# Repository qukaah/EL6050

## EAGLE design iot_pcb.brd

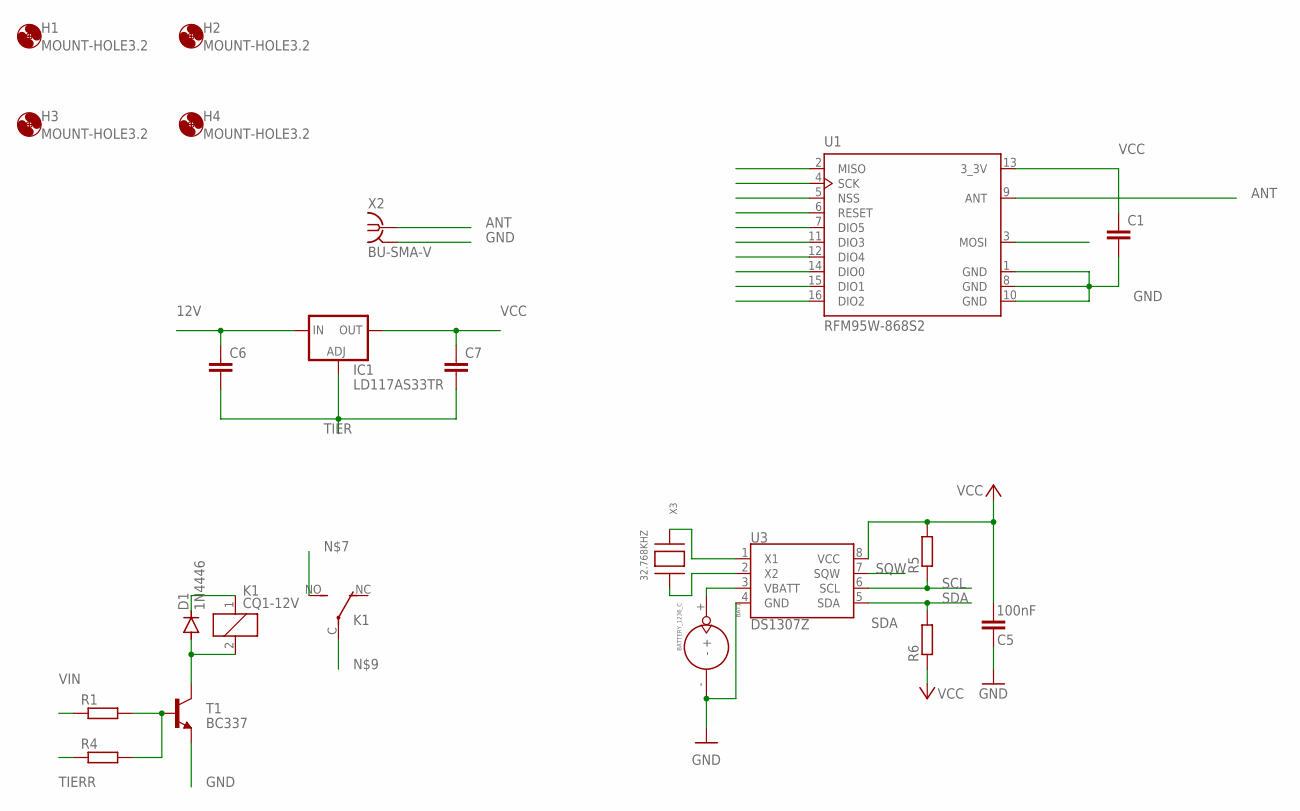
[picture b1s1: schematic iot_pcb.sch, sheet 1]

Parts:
BAT1: BATTERY_1236_C
C1, C6, C7: C-EU050-025X075; C050-025X075
C5: 100nF; C0603
D1: 1N4446; DO35-10
H1, H2, H3, H4: MOUNT-HOLE3.2; 3,2
IC1: LD117AS33TR; SOT223
K1: CQ1-12V; CQ1
R1, R4, R5, R6: R-EU_0207/10; 0207/10
T1: BC337; TO92
U1: RFM95W-868S2; XCVR_RFM95W-868S2
U3: DS1307Z; SO08-0.15
X2: BU-SMA-V
X3: 32.768KHZ; XTAL3215

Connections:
12V: C6.1, IC1.3 (IN)
ANT: U1.9 (ANT), X2.1
GND: BAT1.-, C1.2, C5.1, T1.1 (E), U1.1 (GND), U1.8 (GND), U1.10 (GND), U3.4 (GND), X2.2, X2.3 (2), X2.4 (2), X2.5 (2); also elsewhere on the board
unnamed: BAT1.+, U3.3 (VBATT)
unnamed: U3.1 (X1), X3.P$2
unnamed 13: K1.NO (S); also elsewhere on the board
unnamed 15: K1.C; also elsewhere on the board
unnamed: U3.2 (X2), X3.P$1
unnamed: D1.A, K1.2, T1.3 (C)
unnamed: D1.C, K1.1
unnamed: R1.2, R4.2, T1.2 (B)
SCL: R5.1, U3.6 (SCL)
SDA: R6.2, U3.5 (SDA)
SQW: U3.7 (SQW)
TIER: C6.2, C7.2, IC1.1 (ADJ)
TIERR: R4.1
VCC: C1.1, C5.2, C7.1, IC1.4 (OUT), R5.2, R6.1, U1.13 (3_3V), U3.8 (VCC)
VIN: R1.1

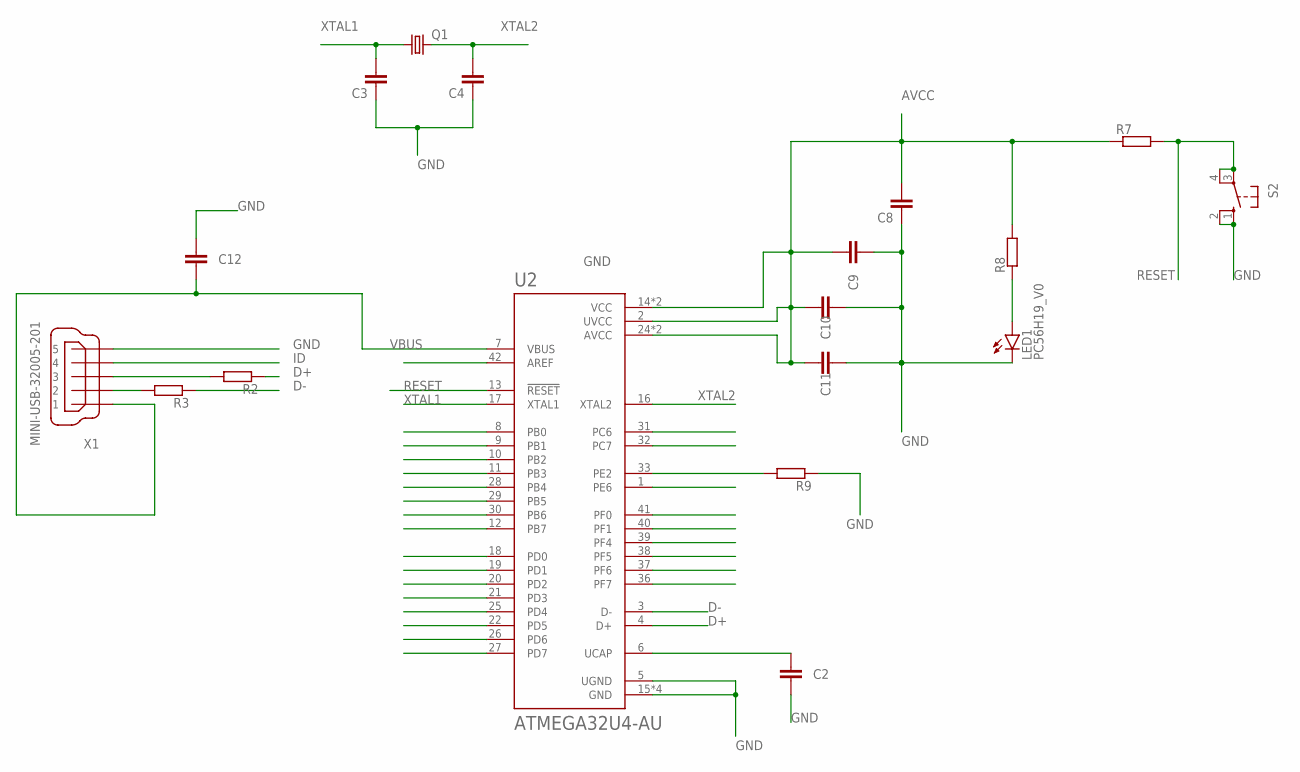
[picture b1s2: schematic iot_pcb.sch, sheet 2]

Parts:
C2, C3, C4, C8, C9, C10, C11, C12: C-EU050-025X075; C050-025X075
LED1: PC56H19_V0
Q1: CRYSTALHC49S; HC49/S
R2, R3, R7, R8, R9: R-EU_0204/7; 0204/7
S2: 40-XX; B3F-40XX
U2: ATMEGA32U4-AU; QFP80P1200X1200X120-44N
X1: MINI-USB-32005-201; 32005-201

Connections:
AVCC: C8.2, C9.2, C10.2, C11.1, R7.1, R8.2, U2.2 (UVCC), U2.14 (VCC), U2.24 (AVCC), U2.34 (VCC), U2.44 (AVCC)
D+: R2.1, U2.4 (D+)
D-: R3.1, U2.3 (D-)
GND: C2.2, C3.1, C4.1, C8.1, C9.1, C10.1, C11.2, C12.1, LED1.1 (C), LED1.3 (C), R9.1, S2.1 (S), S2.2 (S1), U2.5 (UGND), U2.15 (GND), U2.23 (GND), U2.35 (GND), U2.43 (GND), X1.5; also elsewhere on the board
ID: X1.4
unnamed: C2.1, U2.6 (UCAP)
unnamed 13: U2.10 (PB2); also elsewhere on the board
unnamed 15: U2.28 (PB4); also elsewhere on the board
unnamed: R3.2, X1.2
unnamed: R2.2, X1.3
unnamed: R9.2, U2.33 (PE2)
unnamed: LED1.2 (A), LED1.4 (A), R8.1
RESET: R7.2, S2.3, S2.4 (P1), U2.13 (!RESET)
VBUS: C12.2, U2.7 (VBUS), X1.1
XTAL1: C3.2, Q1.1, U2.17 (XTAL1)
XTAL2: C4.2, Q1.2, U2.16 (XTAL2)

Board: 2 copper layers, 39 parts (0 on the bottom side), 27 nets, no tracks yet.

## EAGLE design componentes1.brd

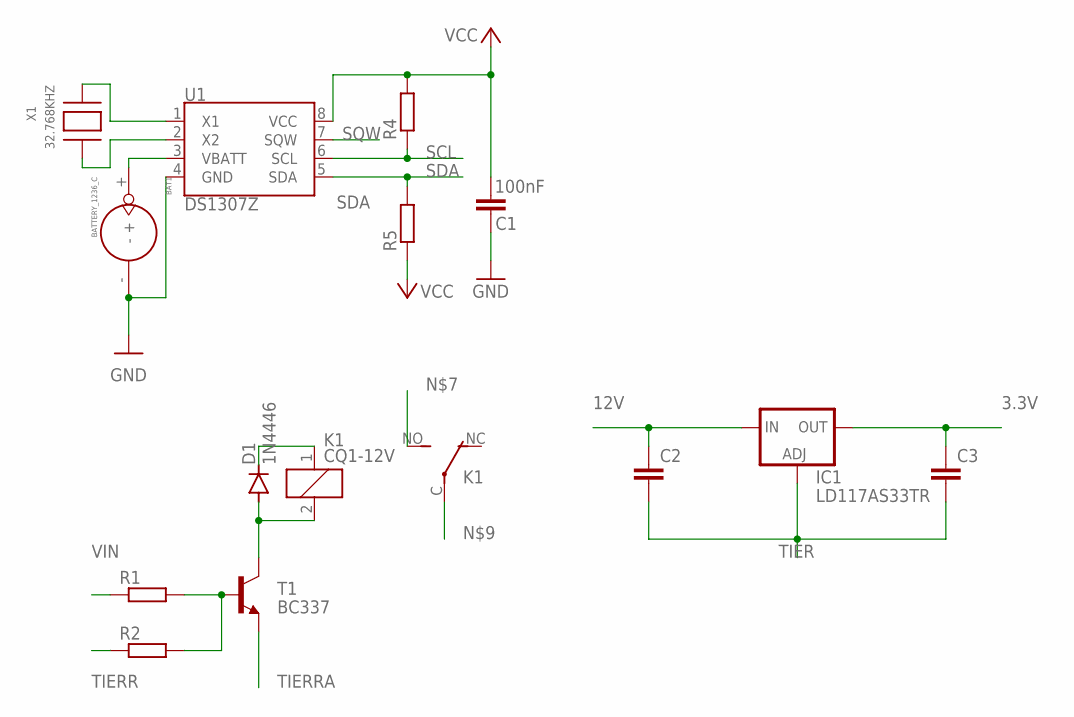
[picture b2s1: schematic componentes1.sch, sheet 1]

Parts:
BAT1: BATTERY_1236_C
C1: 100nF; C0603
C2, C3: C-EU050-025X075; C050-025X075
D1: 1N4446; DO35-10
IC1: LD117AS33TR; SOT223
K1: CQ1-12V; CQ1
R1, R2, R4, R5: R-EU_0207/10; 0207/10
T1: BC337; TO92
U1: DS1307Z; SO08-0.15
X1: 32.768KHZ; XTAL3215

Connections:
3.3V: C3.1, IC1.4 (OUT); also elsewhere on the board
12V: C2.1, IC1.3 (IN)
GND: BAT1.-, C1.1, U1.4 (GND); also elsewhere on the board
unnamed: U1.1 (X1), X1.P$2
unnamed: U1.2 (X2), X1.P$1
unnamed: D1.A, K1.2, T1.3 (C)
unnamed: BAT1.+, U1.3 (VBATT)
unnamed: D1.C, K1.1
unnamed: R1.2, R2.2, T1.2 (B)
SCL: R4.1, U1.6 (SCL)
SDA: R5.2, U1.5 (SDA)
SQW: U1.7 (SQW)
TIER: C2.2, C3.2, IC1.1 (ADJ)
TIERR: R2.1
TIERRA: T1.1 (E)
VCC: C1.2, R4.2, R5.1, U1.8 (VCC); also elsewhere on the board
VIN: R1.1

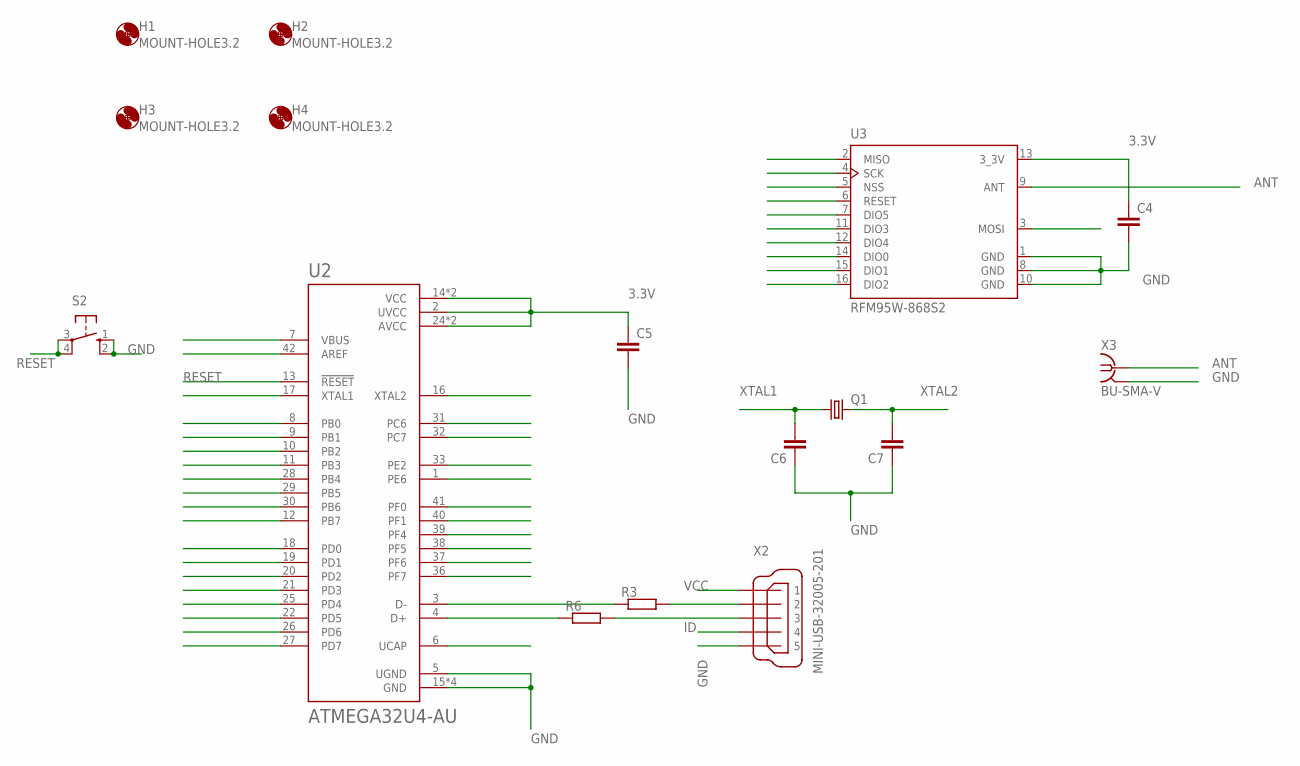
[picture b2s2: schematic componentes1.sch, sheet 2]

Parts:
C4, C5, C6, C7: C-EU050-025X075; C050-025X075
H1, H2, H3, H4: MOUNT-HOLE3.2; 3,2
Q1: CRYSTALHC49S; HC49/S
R3, R6: R-EU_0204/7; 0204/7
S2: 40-XX; B3F-40XX
U2: ATMEGA32U4-AU; QFP80P1200X1200X120-44N
U3: RFM95W-868S2; XCVR_RFM95W-868S2
X2: MINI-USB-32005-201; 32005-201
X3: BU-SMA-V

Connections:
3.3V: C4.1, C5.1, U2.2 (UVCC), U2.14 (VCC), U2.24 (AVCC), U2.34 (VCC), U2.44 (AVCC), U3.13 (3_3V); also elsewhere on the board
ANT: U3.9 (ANT), X3.1
GND: C4.2, C5.2, C6.1, C7.1, S2.1 (S), S2.2 (S1), U2.5 (UGND), U2.15 (GND), U2.23 (GND), U2.35 (GND), U2.43 (GND), U3.1 (GND), U3.8 (GND), U3.10 (GND), X2.5, X3.2, X3.3 (2), X3.4 (2), X3.5 (2); also elsewhere on the board
ID: X2.4
unnamed: R3.1, U2.3 (D-)
unnamed: R3.2, X2.2
unnamed: R6.2, X2.3
unnamed: R6.1, U2.4 (D+)
RESET: S2.3, S2.4 (P1), U2.13 (!RESET)
VCC: X2.1; also elsewhere on the board
XTAL1: C6.2, Q1.1
XTAL2: C7.2, Q1.2

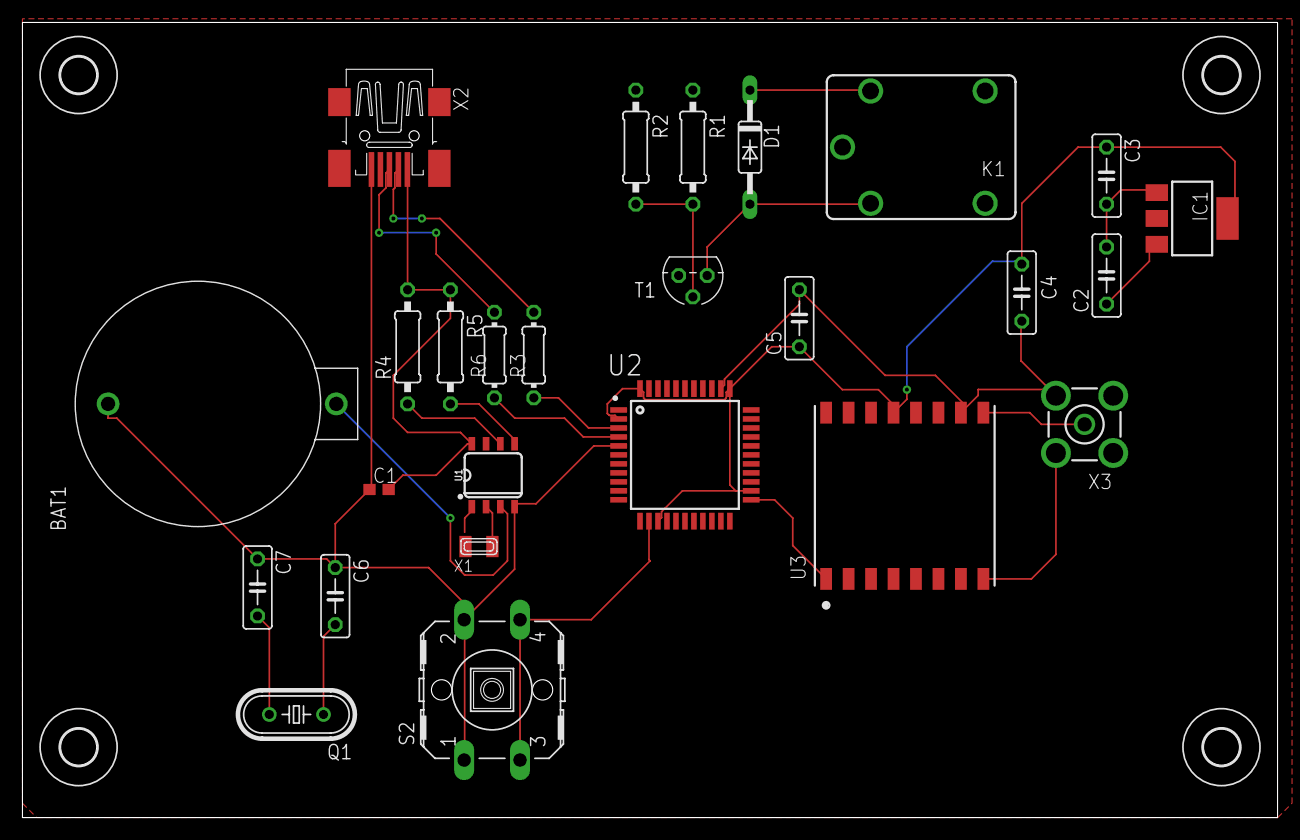
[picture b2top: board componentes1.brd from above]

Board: 2 copper layers, 111.7 x 70.8 mm, 30 parts (0 on the bottom side), 21 nets.

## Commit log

2022-06-07 primer commit
2022-06-07 Se termina RTC, REG.voltaje y Rele
2022-06-07 renombre esquematico -> componentes1
2022-06-07 archivos chela
2022-06-09 se agrega board
2022-06-09 xfabo no c muera
2022-06-09 bordes board

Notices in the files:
parts and their libraries:
SparkFun-Clocks: Licensing: Creative Commons ShareAlike 4.0 International - https://creativecommons.org/licenses/by-sa/4.0
